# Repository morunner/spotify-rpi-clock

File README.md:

# spotify-rpi-clock

The alarm clock should consist of two components - hardware and software. It should provide a web (or app) interface where
one can set wake-up songs, albums, artists and/or playlists. It should also enable selecting a playback device and setting its volume. Furthermore, one should be able to set the volume and activate the clock in hardware
by means of knobs and potentiometers.

## Components
### Hardware

| Component                          | Description                                            |
|------------------------------------|--------------------------------------------------------|
| Raspberry Pi Zero                  | For the Spotify connect client                         |
| Adafruit I2S 3W Speaker Bonnet     | Audio Interface between speakers and Raspberry Pi Zero |
| 2x Visaton SC 5.9 ND 4 Ohm Speaker | Speakers playing the audio                             |
| Push buttons, Potentiometers, LEDs | For fast control, still TBD                            |

### Software

#### Spotify Client
There are two options to make the Raspberry Pi Zero a Spotify Client:
    - cspot: https://github.com/feelfreelinux/cspot
    - spotifyd (librespot): https://github.com/Spotifyd/spotifyd (https://github.com/librespot-org/librespot)
They are still to be evaluated

#### Backend
Supabase is used.

#### Frontend: Webapp
The Web-UI is written in dart using flutter.

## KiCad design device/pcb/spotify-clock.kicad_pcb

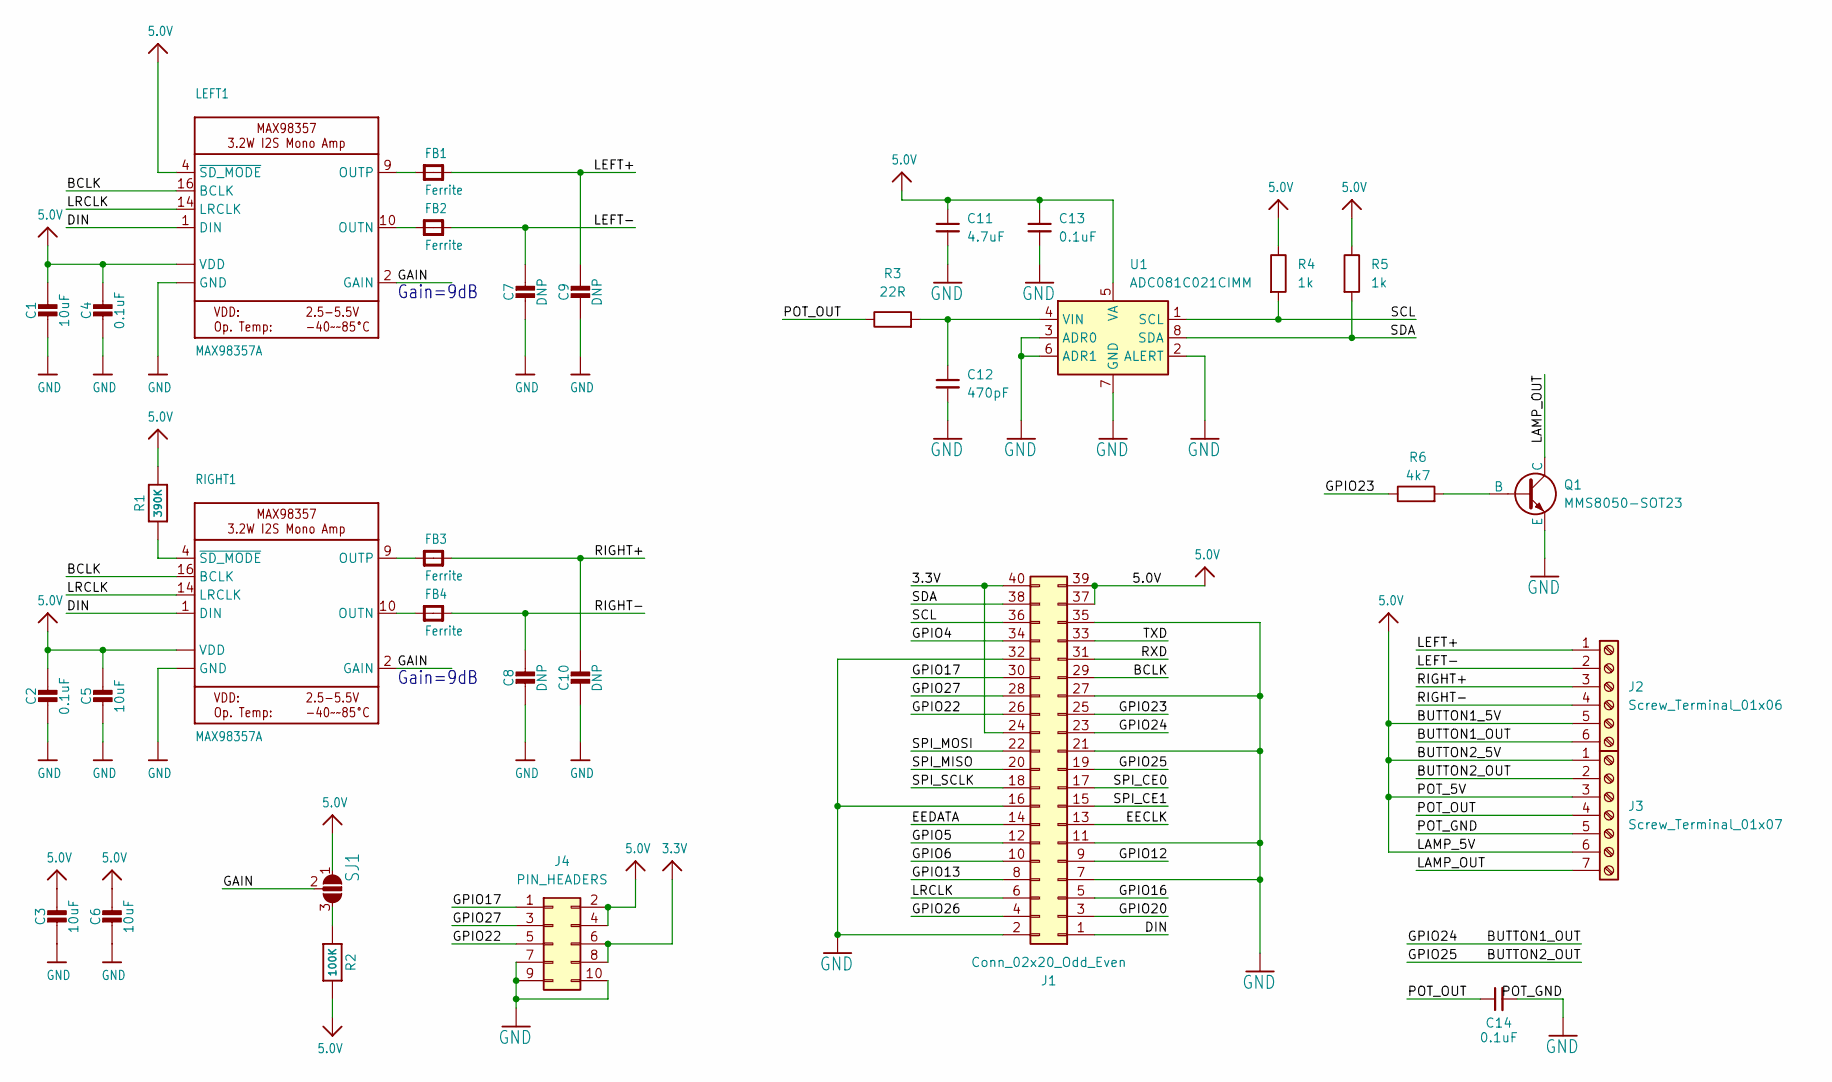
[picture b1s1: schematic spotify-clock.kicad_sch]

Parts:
C1, C3, C5, C6: 10uF; 0805-NO
C2, C4, C13, C14: 0.1uF; 0805-NO
C7, C8, C9, C10: DNP; 0805-NO
C11: 4.7uF; 0805-NO
C12: 470pF; 0805-NO
FB1, FB2, FB3, FB4: Ferrite; 0805-NO
J1: Conn_02x20_Odd_Even; PinSocket_2x20_P2.54mm_Vertical_SMD
J2: Screw_Terminal_01x06; TerminalBlock_TE_282834-6_1x06_P2.54mm_Horizontal
J3: Screw_Terminal_01x07; TerminalBlock_TE_282834-7_1x07_P2.54mm_Horizontal
J4: PIN_HEADERS; PinHeader_2x05_P2.54mm_Vertical
LEFT1: MAX98357A; QFN16_3MM
Q1: MMS8050-SOT23; TSOT-23
R1: 390K; 0805-NO
R2: 100K; 0805-NO
R3: 22R; 0805-NO
R4, R5: 1k; 0805-NO
R6: 4k7; 0805-NO
RIGHT1: MAX98357A; QFN16_3MM
SJ1: SOLDERJUMPER_2WAY; SOLDERJUMPER_2WAY_OPEN_NOPASTE
U1: ADC081C021CIMM; MSOP-8_3x3mm_P0.65mm

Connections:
3.3V: J1.24, J1.40, J4.6, J4.8
5.0V: C1.1, C2.1, C3.1, C4.1, C5.1, C6.1, C11.1, C13.1, J1.37, J1.39, J2.5, J3.1, J3.3, J3.6, J4.2, J4.4, LEFT1.4 (~SD_MODE), LEFT1.7 (VDD), LEFT1.8 (VDD), R1.2, R2.2, R4.1, R5.1, RIGHT1.7 (VDD), RIGHT1.8 (VDD), SJ1.1, U1.5 (VA)
/BCLK: J1.29, LEFT1.16 (BCLK), RIGHT1.16 (BCLK)
/BUTTON1_OUT: J1.23, J2.6
/BUTTON2_OUT: J1.19, J3.2
/DIN: J1.1, LEFT1.1 (DIN), RIGHT1.1 (DIN)
/EECLK: J1.13
/EEDATA: J1.14
/GAIN: LEFT1.2 (GAIN), RIGHT1.2 (GAIN), SJ1.2
/GPIO4: J1.34
/GPIO5: J1.12
/GPIO6: J1.10
/GPIO12: J1.9
/GPIO13: J1.8
/GPIO16: J1.5
/GPIO17: J1.30, J4.1
/GPIO20: J1.3
/GPIO22: J1.26, J4.5
/GPIO23: J1.25, R6.1
/GPIO26: J1.4
/GPIO27: J1.28, J4.3
/LAMP_OUT: J3.7, Q1.1 (C)
/LEFT+: C9.1, FB1.2, J2.1
/LEFT-: C7.1, FB2.2, J2.2
/LRCLK: J1.6, LEFT1.14 (LRCLK), RIGHT1.14 (LRCLK)
/POT_OUT: C14.1, J3.4, R3.1
/RIGHT+: C10.1, FB3.2, J2.3
/RIGHT-: C8.1, FB4.2, J2.4
/RXD: J1.31
/SCL: J1.36, R4.2, U1.1 (SCL)
/SDA: J1.38, R5.2, U1.8 (SDA)
/SPI_CE0: J1.17
/SPI_CE1: J1.15
/SPI_MISO: J1.20
/SPI_MOSI: J1.22
/SPI_SCLK: J1.18
/TXD: J1.33
GND: C1.2, C2.2, C3.2, C4.2, C5.2, C6.2, C7.2, C8.2, C9.2, C10.2, C11.2, C12.2, C13.2, C14.2, J1.2, J1.7, J1.11, J1.16, J1.21, J1.27, J1.32, J1.35, J3.5, J4.7, J4.9, J4.10, LEFT1.3 (GND), LEFT1.11 (GND), LEFT1.15 (GND), LEFT1.THERMAL (GND), Q1.3 (E), RIGHT1.3 (GND), RIGHT1.11 (GND), RIGHT1.15 (GND), RIGHT1.THERMAL (GND), U1.2 (ALERT), U1.3 (ADR0), U1.6 (ADR1), U1.7 (GND)
unnamed: FB1.1, LEFT1.9 (OUTP)
unnamed: FB2.1, LEFT1.10 (OUTN)
unnamed: FB3.1, RIGHT1.9 (OUTP)
unnamed: FB4.1, RIGHT1.10 (OUTN)
unnamed: Q1.2 (B), R6.2
unnamed: R2.1, SJ1.3
unnamed: R1.1, RIGHT1.4 (~SD_MODE)
unnamed: C12.1, R3.2, U1.4 (VIN)

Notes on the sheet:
Gain=9dB

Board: 2 copper layers, 33 parts (1 on the bottom side), 29 nets, no tracks yet.

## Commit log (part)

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2023-01-02 + api
2023-01-02 + db
2023-01-02 + app main
2023-07-15 add flutter Dockerfile and devcontainer settings
2023-07-15 move backend files
2023-07-15 add docs openapi yml db_model description for requirements
2023-07-15 init frontend flutter app
2023-07-15 add font style
2023-07-15 add main.dart by adding .gitignore
2023-07-21 refactor code one folder per page there, also page-specific components should be located
2023-07-21 add custom tool bar class
2023-07-21 add project name
2023-07-23 add getx functionality skeleton
2023-07-23 remove unexisting entry from pubspec dependencies
2023-07-23 add clock entry feature to home controller
2023-07-23 change routes
2023-07-23 add listview to display some test lines add/delete funcitonality
2023-07-23 refactor custom appbar create components folder move to different file in components
2023-07-23 add artist and adjust listtile text style
2023-08-07 add trash icon hover effect
2023-08-08 experiment with sliding_up_panel
2023-08-08 add clock entries list (#1)
    * add clock entry data model
    * remove unexisting entry from pubspec dependencies
    * add clock entry feature to home controller
    * change routes
    * add listview to display some test lines
    add/delete funcitonality
2023-08-08 add first supabase functionality
2023-08-08 add first supabase connection (#3)
2023-08-08 init skeleton
2023-08-08 move supabase credentials to .env file
2023-08-08 remove clock entry from homecontroller now in addentrycontroller
2023-08-08 fix small errors in home_view
2023-08-08 add navigation also enable saving of clockEntry by pressing fertig
2023-08-08 add cupertinodatepicker and start with song display
2023-08-10 simplify code (#4)
    remove getx and use plain flutter functionalities
2023-08-12 add shuffle/volume control and device menu layout
2023-08-12 add album display layout
2023-08-12 modify font sizes and spacings
2023-08-12 refactor - create inner shadow container
2023-08-12 fix infinite height for datetimepicker
2023-08-12 re-add cupertino package
2023-08-13 add clock entry menu first layout (#6)
    * init skeleton
    * move supabase credentials to .env file
    * add individual setter function for each clock entry property
    * remove clock entry from homecontroller
    now in addentrycontroller
    * fix small errors in home_view
2023-08-21 move clock entry stream to ClockEntryManager
2023-08-21 add Spotify client using Supabase OAuth
2023-08-21 fix GlobalKey Navigation error when coming back after Spotify Login Page
2023-08-21 Connect spotify (#7)
    * update pubspec.lock
    * add forwarded port to run flutter in web
    also set Dart: Flutter Run Additional Args
    --web-port=5000 in VSCode settings.
    Enable access in chrome browser on localhost:5000.
    Needs Dart debug extension installed.
2023-08-21 init spotify client
2023-08-21 make add entry menu stateful
2023-08-21 create dialog for searching for and adding a song
2023-08-23 fix typeahead field listtile text color
2023-08-27 add store and load most recent selection in add entry menu
2023-08-27 create spotify song select dialog (#8)
    * create separate class for clock entry
    * init spotify client
    * make add entry menu stateful
    * create dialog for searching for and adding a song
    * fix typeahead field listtile text color
    * add store and load most recent selection
2023-08-27 change variables to lowerCamelCase
2023-08-27 create common folder for widgets
2023-08-27 rename screen files
2023-08-27 create separate widget for clockEntriesList
2023-08-27 create global style scheme
2023-08-27 rename file
2023-08-27 move wakeup time picker to separate file
2023-08-27 move device settings to dedicated widget
2023-08-27 rename clockEntryManager to BackendInterface
2023-08-27 cleanup repo remove deprecated content
2023-08-27 refactor flutter code and cleanup repo (#9)
    * change variables to lowerCamelCase
    * create common folder for widgets
    * rename screen files
    * create data folder
    * create separate widget for clockEntriesList
    * create global style scheme
2023-08-31 use Uri.https to create uri
2023-08-31 add device class and fetch available devices
2023-08-31 only store track_id and device_id get other values from spotify api when needed
2023-08-31 only store track_id and device_id (#13)
    get other values from spotify api when needed
2023-08-31 display selected device after click in dropdown
2023-08-31 set device selected by default if no other clicked return only text if no device available
2023-09-05 remove deprecated code
2023-09-05 Feature/select spotify connect device (#17)
    * remove unused variable
    * use Uri.https to create uri
    * add device class and fetch available devices
    * only store track_id and device_id (#13)
    get other values from spotify api when needed
    * display selected device in list
2023-09-05 set device to first in list upon refresh
2023-09-05 Fix/disallow no device (#19)
    * create alert dialog
    clear device upon save to prevent conflicts
    when device becomes unavailable when in
    list menu
    * set device to first in list upon refresh
2023-09-05 add authenticator provides signed in state
2023-09-05 add login/logout functionality
2023-09-05 set max width of clock entry add menu
2023-09-05 Feature/logout option (#23)
    * add authenticator
    provides signed in state
    * add login/logout functionality
    * set max width of clock entry add menu
    * replace cancel by ok
2023-09-05 enable/disable clock entry by id
2023-09-05 refactor divide widgets into classes
2023-09-05 Feature/enable disable entries (#24)
    * enable/disable clock entry by id
    * refactor
    divide widgets into classes
2023-09-05 replace default value by hint (#26)
2023-09-08 also match user_uid to only display data which belongs to the signed-in user
2023-09-08 also match user_uid (#30)
    to only display data which belongs to the signed-in user
2023-09-11 initial flutter app (#31)
    * add auto_size_text package
    * refactor code
    one folder per page
    there, also page-specific components should be located
    * add custom tool bar class
    * add project name
2023-09-12 fix backendInterface error (#34)
    by loading most recent selection only in
    song_select, when user is already signed in
    and session exists.
2023-09-12 fix second backendInterface returning null fixes a newly discovered issue already addressed in #32
2023-09-12 store provider_token and provider_refresh_token for user
2023-09-12 upload spotify tokens for each user (#35)
    * fix second backendInterface returning null
    fixes a newly discovered issue already addressed in #32
    * store provider_token and provider_refresh_token for user
    closes #33
2023-09-14 fix base href on workflow for web app build
2023-09-14 create .env file from secrets on build
2023-09-14 modify workdirs
2023-09-14 replace github pages by netlify
2023-09-14 move .env to assets
2023-09-14 Revert "move .env to assets"
    This reverts commit ae3c7f5bf37f1de6697529595be31b9d1ed745b2.
2023-09-14 modify env variable reading for deployment remove .env and replace by env variables
2023-09-14 fix flutter errors upon deployment (#37)
    * Revert "move .env to assets"
    This reverts commit ae3c7f5bf37f1de6697529595be31b9d1ed745b2.
    * modify env variable reading for deployment
    remove .env and replace by env variables
2023-09-14 fix build make flutter build command one-liner move env vars
2023-09-14 add function to fetch spotify access token from refresh token
2023-09-14 add supabase configs
2023-09-14 add utc offset when inserting in database for check in backend if clock should be activated
2023-09-14 enable playback scope for spotify API
2023-09-14 remove unused import
2023-09-14 play on spotify connect device (#38)
    * init supabase function
    * add function to fetch spotify access token from refresh token
    * enable playback scope for spotify API
    * add utc offset when inserting in database
    for check in backend if clock should be activated
    * update supabase .gitignore
2023-09-14 delete entry by id instead of track id (#40)
    avoid deleting all entries with the same track
2023-09-15 modify app name, description and icon
2023-09-15 style modifications (#42)
    * modify app name, description and icon
    * fix cupertinodatepicker font family and color
2023-09-15 rename get function and move getting provider token to authenticator
2023-09-15 add build and deploy status badge
2023-09-19 trim pattern for whitespaces
2023-10-14 add first rudimentary working connect device
2023-10-14 link project for rust-analyzer
2023-10-14 add play/pause functionality using keyboard input
2023-10-14 add librespot library
2023-10-14 add devcontainer for rust also revise flutter devcontainer settings
2023-10-14 add rpi gpio set example
2023-10-14 fix blinking LED start prep for reading button input
2023-10-14 fix cross-compilation for rpi zero
2023-10-14 add .gitignore for device part of the project
2023-10-14 enable reading button and potentiometer play/pause/volume detect
2023-10-18 init volume control not working yet
2023-10-18 move spotify client init to separate file
2023-10-18 move hw access to peripherals comment out volume ctl related code as this is not working yet
2023-11-03 create struct for play/pause button to keep states and create separate loop
2023-11-03 create struct for volumecontroller
    still missing working functionality
2023-11-04 fix volume control
2023-11-04 move setting led to playbackcontroller
2023-11-04 enable setting volume from smartphone
    todo: fix interference between smartphone and potentiometer volume
    control
2023-11-05 spawn tasks in main
2023-11-05 basic functionality for all clock hardware peripherals (#52)
    * enable reading button and potentiometer
    play/pause/volume detect
    * init volume control
    not working yet
    * move spotify client init to separate file
    * move hw access to peripherals
2023-11-11 feat: add systemd service
2023-11-12 Feature/54 create systemd service for spotify client (#55)
    * feat: add systemd service
    * feat: get credentials from environment variables loaded from systemd service
2023-11-12 feat: add asound.conf for Adafruit speaker bonnet
    tested with Raspberry Pi 2 W
    taken from adafruit speaker bonnet raspi setup script
    https://raw.githubusercontent.com/adafruit/Raspberry-Pi-Installer-Scripts/master/i2samp.sh
2023-11-12 fix: add After: to systemd
    start program after complete boot process of Pi
    see https://www.freedesktop.org/software/systemd/man/latest/systemd.special.html
    for details on multi-user.target
2023-11-12 Fix/56 adafruit speaker bonnet driver installation (#57)
    * feat: add asound.conf for Adafruit speaker bonnet
    tested with Raspberry Pi 2 W
    taken from adafruit speaker bonnet raspi setup script
    https://raw.githubusercontent.com/adafruit/Raspberry-Pi-Installer-Scripts/master/i2samp.sh
    * fix: add After: to systemd
    start program after complete boot process of Pi
2024-02-07 fix(app): select most recent track based on update time instead of id (#59)
    This allows the most recent song selection to load correctly if the row id
    changes.
2024-02-09 feat(device): update cargo.toml
2024-02-10 refactor(device): create separate struct for keyboard readout
2024-02-12 refactor(device): restructure volume readout via keyboard
2024-02-13 feat(device): add argparsing for log level and input type
2024-02-19 feat(device): add ability to read adc and use config, argparser
2024-02-19 fix(device): Use dev branch from librespot
    To allow setting volume through Spirc. Bug tradeoff: Unable to set volume
    in Spotify on iPhone when connected.
2024-02-19 feat(device): support play/pause button and add config file
2024-02-20 feat(device): Add status LED support and set volume at play cmd
2024-02-27 feat(device): add player event handler
2024-02-27 Fix/60 mock hardware for spotify client (#61)
    * feat(device): update cargo.toml
    * update .gitignores
    * refactor(device): create separate struct for keyboard readout
    * refactor(device): restructure volume readout via keyboard
    * refactor(device): Support play/pause commands with keyboard
    * feat(device): add argparsing for log level and input type
2024-03-21 add adapted adafruit speaker bonnet schematic
    imported from eagleCAD to kiCAD
    added adc for potentiometer,
    screw terminal for all peripherals
